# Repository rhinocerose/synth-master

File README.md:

# Synth Resouorce (Mostly Eurorack)

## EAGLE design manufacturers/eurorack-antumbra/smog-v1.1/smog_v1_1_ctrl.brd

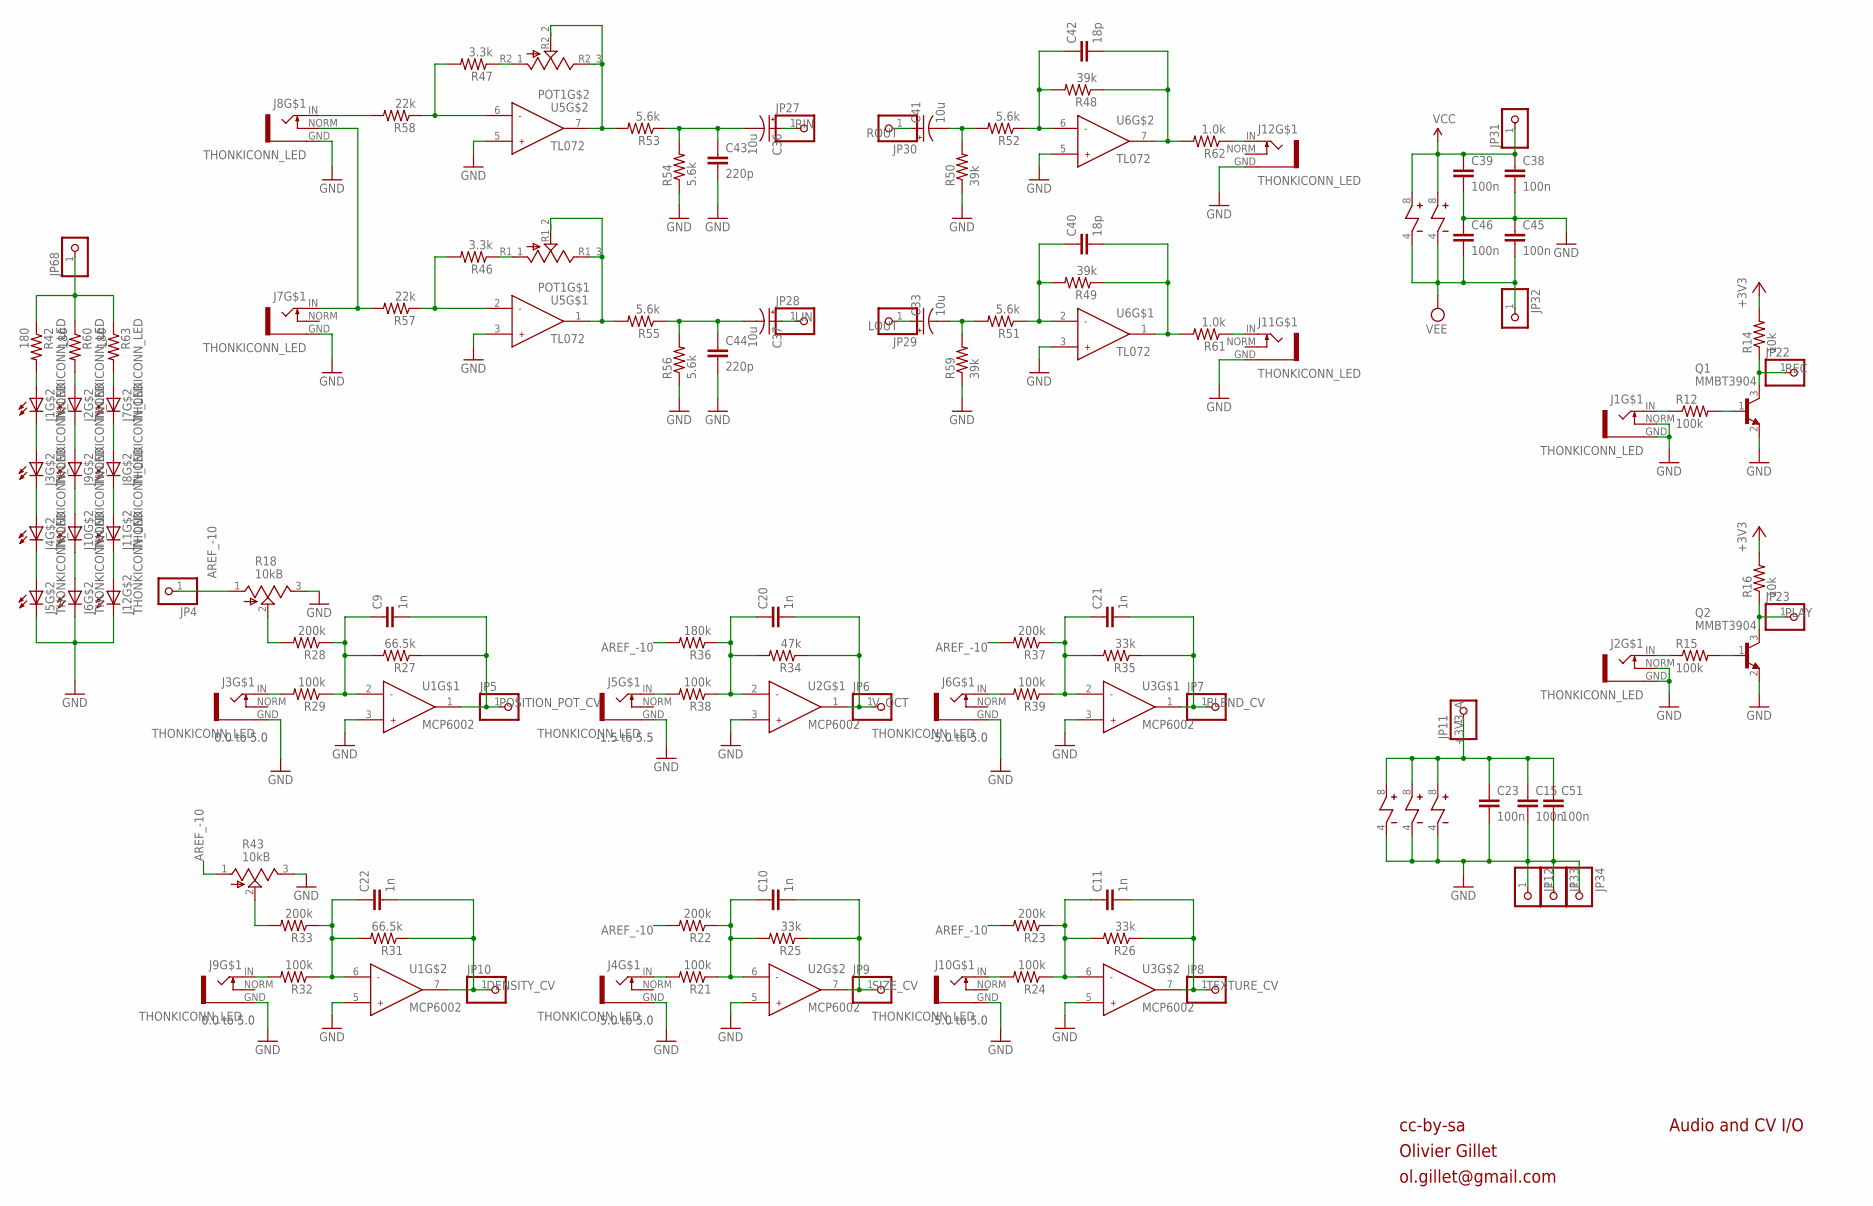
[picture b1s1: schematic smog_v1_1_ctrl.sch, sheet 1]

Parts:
C9, C10, C11, C20, C21, C22: 1n; RESISTOR_0603
C15, C23, C38, C39, C45, C46, C51: 100n; RESISTOR_0603
C33, C36, C37, C41: 10u; PANASONIC_B
C40, C42: 18p; RESISTOR_0603
C43, C44: 220p; RESISTOR_0603
J1, J2, J3, J4, J5, J6, J7, J8, J9, J10, J11, J12: THONKICONN_LED; LED_JACK
JP4, JP5, JP6, JP7, JP8, JP9, JP10, JP11, JP12, JP22, JP23, JP27, JP28, JP29, JP30, JP31, JP32, JP33, JP34, JP68: PINHD-1X1; 1X01
POT1: POT_DUAL_THONK
Q1, Q2: MMBT3904; SOT23
R12, R15, R21, R24, R29, R32, R38, R39: 100k; RESISTOR_0603
R14, R16: 10k; RESISTOR_0603
R18, R43: 10kB; ALPS_POT_VERTICAL
R22, R23, R28, R33, R37: 200k; RESISTOR_0603
R25, R26, R35: 33k; RESISTOR_0603
R27, R31: 66.5k; RESISTOR_0603
R34: 47k; RESISTOR_0603
R36: 180k; RESISTOR_0603
R42, R60, R63: 180; RESISTOR_0603
R46, R47: 3.3k; RESISTOR_0603
R48, R49, R50, R59: 39k; RESISTOR_0603
R51, R52, R53, R54, R55, R56: 5.6k; RESISTOR_0603
R57, R58: 22k; RESISTOR_0603
R61, R62: 1.0k; RESISTOR_0603
U1, U2, U3: MCP6002; SOIC8
U5, U6: TL072; SOIC8

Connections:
+3V3: R14.2, R16.2; also elsewhere on the board
+3V3_A: C15.1, C23.1, C51.1, JP11.1, U1.8, U2.8, U3.8; also elsewhere on the board
AREF_-10: JP4.1, R18.1 (A), R22.2, R23.2, R36.2, R37.2, R43.1 (A)
BLEND_CV: C21.2, JP7.1, R35.1, U3.1
DENSITY_CV: C22.2, JP10.1, R31.1, U1.7
GND: C15.2, C23.2, C38.2, C39.2, C43.2, C44.2, C45.1, C46.1, C51.2, J1.GND, J1.NORM, J2.GND, J2.NORM, J3.GND, J4.GND, J5.C, J5.GND, J6.C, J6.GND, J7.GND, J8.GND, J9.GND, J10.GND, J11.GND, J12.C, J12.GND, JP12.1, JP33.1, JP34.1, Q1.2 (E), Q2.2 (E), R18.3 (B), R43.3 (B), R50.1, R54.1, R56.1, R59.1, U1.3, U1.4, U1.5, U2.3, U2.4, U2.5, U3.3, U3.4, U3.5, U5.3, U5.5, U6.3, U6.5; also elsewhere on the board
LIN: C37.+, JP28.1
LOUT: C33.+, JP29.1
LOUT_JACK: J11.IN, R61.1
unnamed: J4.IN, R21.2
unnamed: C10.1, R21.1, R22.1, R25.2, U2.6
unnamed: J1.C, J3.A
unnamed: J10.IN, R24.2
unnamed: C11.1, R23.1, R24.1, R26.2, U3.6
unnamed: J6.IN, R39.2
unnamed: J3.C, J4.A
unnamed: J4.C, J5.A
unnamed: J5.IN, R38.2
unnamed: C20.1, R34.2, R36.1, R38.1, U2.2
unnamed: J2.A, R60.2
unnamed: J9.IN, R32.2
unnamed: C21.1, R35.2, R37.1, R39.1, U3.2
unnamed: J2.C, J9.A
unnamed: C37.-, C44.1, R55.1, R56.2
unnamed: J9.C, J10.A
unnamed: J8.IN, R58.2
unnamed: J7.IN, J8.NORM, R57.2
unnamed: C36.-, C43.1, R53.1, R54.2
unnamed: C41.-, R50.2, R52.2
unnamed: C22.1, R31.2, R32.1, R33.1, U1.6
unnamed: C42.1, R48.2, R52.1, U6.6
unnamed: R33.2, R43.2 (W)
unnamed: J3.IN, R29.2
unnamed: C42.2, R48.1, R62.2, U6.7
unnamed: C9.1, R27.2, R28.1, R29.1, U1.2
unnamed: C33.-, R51.2, R59.2
unnamed: C40.1, R49.2, R51.1, U6.2
unnamed: C40.2, R49.1, R61.2, U6.1
unnamed: R18.2 (W), R28.2
unnamed: J2.IN, R15.1
unnamed: Q2.1 (B), R15.2
unnamed: POT1.R2_2 (W), POT1.R2_3 (B), R53.2, U5.7
unnamed: POT1.R1_2 (W), POT1.R1_3 (B), R55.2, U5.1
unnamed: POT1.R2_1 (A), R47.1
unnamed: POT1.R1_1 (A), R46.1
unnamed: R47.2, R58.1, U5.6
unnamed: J6.A, J10.C
unnamed: J7.A, R63.2
unnamed: J1.IN, R12.1
unnamed: R46.2, R57.1, U5.2
unnamed: J7.C, J8.A
unnamed: J8.C, J11.A
unnamed: J11.C, J12.A
unnamed: J1.A, R42.2
unnamed: Q1.1 (B), R12.2
unnamed: JP68.1, R42.1, R60.1, R63.1
PLAY: JP23.1, Q2.3 (C), R16.1
POSITION_POT_CV: C9.2, JP5.1, R27.1, U1.1
REC: JP22.1, Q1.3 (C), R14.1
RIN: C36.+, JP27.1
ROUT: C41.+, JP30.1
ROUT_JACK: J12.IN, R62.1
SIZE_CV: C10.2, JP9.1, R25.1, U2.7
TEXTURE_CV: C11.2, JP8.1, R26.1, U3.7
VCC: C38.1, C39.1, JP31.1, U5.8, U6.8
VEE: C45.2, C46.2, JP32.1, U5.4, U6.4
V_OCT: C20.2, JP6.1, R34.1, U2.1

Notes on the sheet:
cc-by-sa
Olivier Gillet
ol.gillet@gmail.com
Audio and CV I/O
0.0 to 5.0
-1.5 to 5.5
-5.0 to 5.0

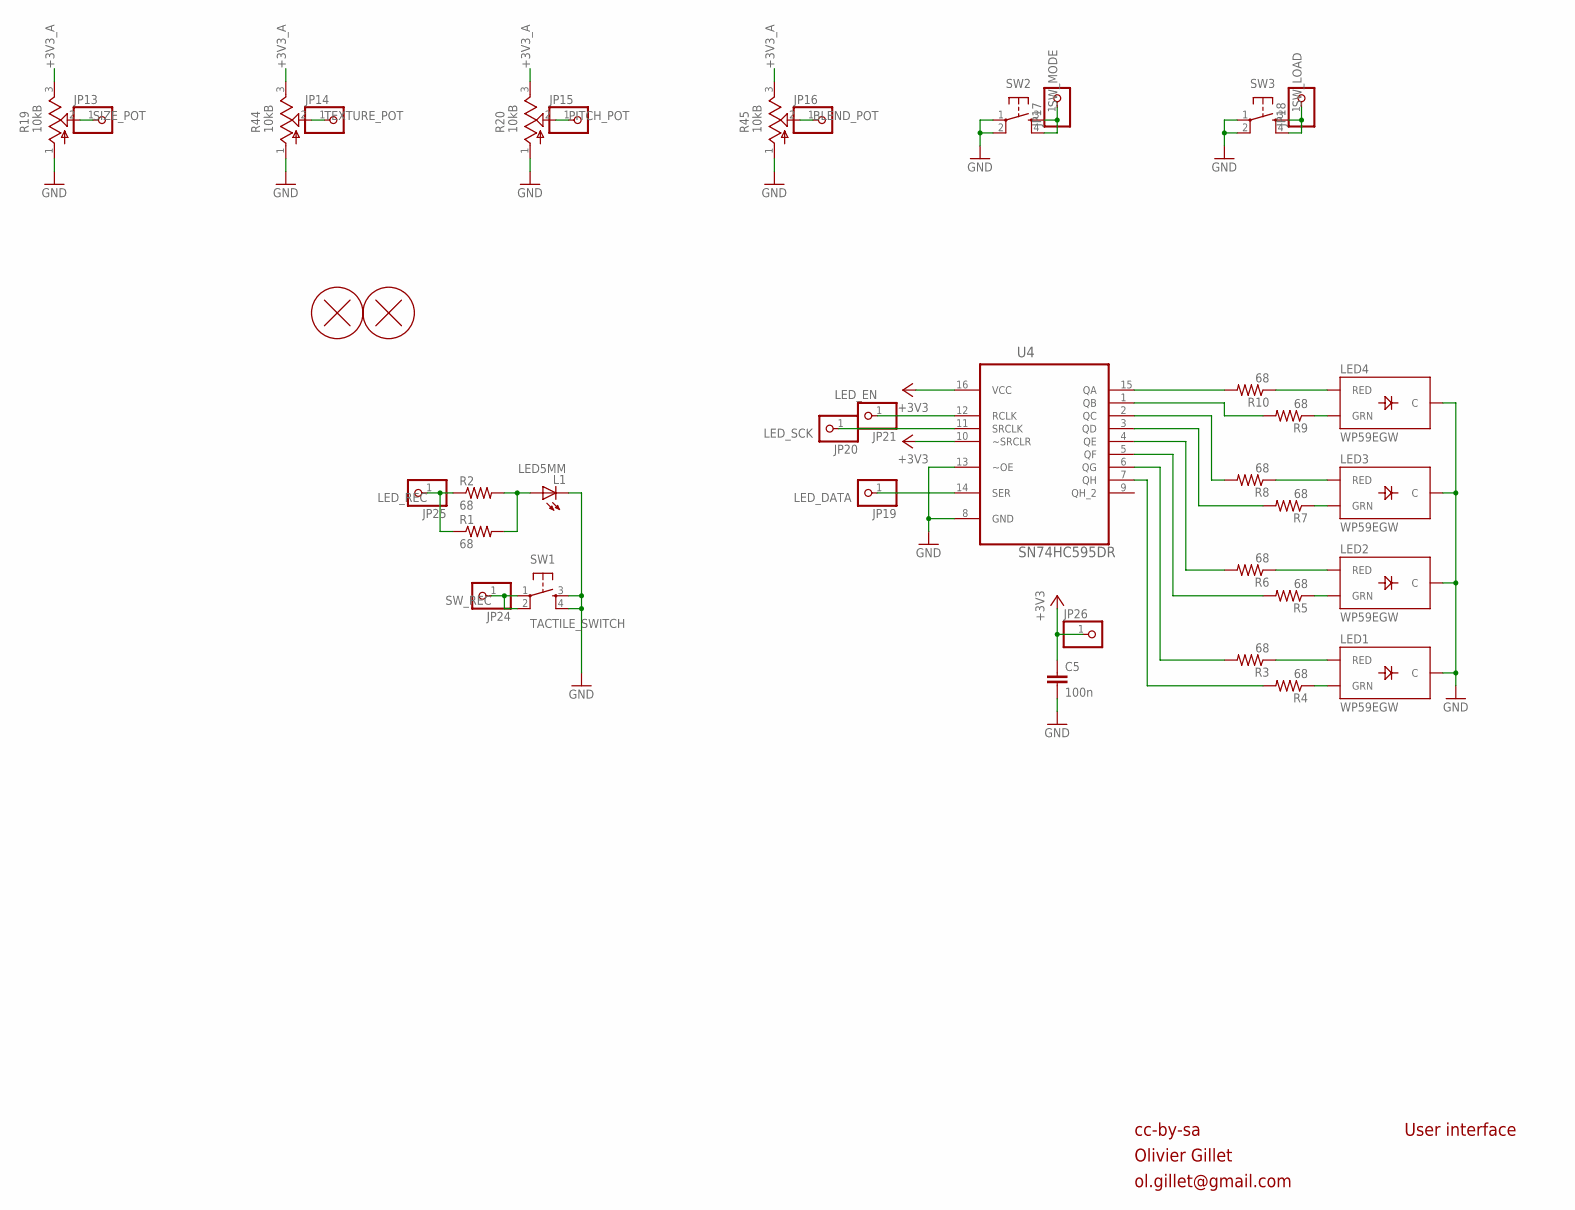
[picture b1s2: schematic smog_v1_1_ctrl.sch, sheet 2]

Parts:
C5: 100n; RESISTOR_0603
H1, H2: PCB_SCREW
JP13, JP14, JP15, JP16, JP17, JP18, JP19, JP20, JP21, JP24, JP25, JP26: PINHD-1X1; 1X01
L1: LED5MM; LED_5MM
LED1, LED2, LED3, LED4: WP59EGW; LED_BICOLOR
R1, R2, R3, R4, R5, R6, R7, R8, R9, R10: 68; RESISTOR_0603
R19, R20, R44, R45: 10kB; ALPS_POT_VERTICAL
SW1, SW2, SW3: TACTILE_SWITCH; TACTILE-PTH
U4: SN74HC595DR; SOIC16

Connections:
+3V3: C5.1, JP26.1, U4.10 (~SRCLR), U4.16 (VCC); also elsewhere on the board
+3V3_A: R19.3 (B), R20.3 (B), R44.3 (B), R45.3 (B); also elsewhere on the board
BLEND_POT: JP16.1, R45.2 (W)
GND: C5.2, L1.K (C), LED1.2 (C), LED2.2 (C), LED3.2 (C), LED4.2 (C), R19.1 (A), R20.1 (A), R44.1 (A), R45.1 (A), SW1.3, SW1.4, SW2.1, SW2.2, SW3.1, SW3.2, U4.8 (GND), U4.13 (~OE); also elsewhere on the board
LED_DATA: JP19.1, U4.14 (SER)
LED_EN: JP21.1, U4.12 (RCLK)
LED_REC: JP25.1, R1.1, R2.1
LED_SCK: JP20.1, U4.11 (SRCLK)
unnamed: LED4.1 (GRN), R9.1
unnamed: LED4.3 (RED), R10.1
unnamed: LED3.3 (RED), R8.1
unnamed: LED3.1 (GRN), R7.1
unnamed: LED2.3 (RED), R6.1
unnamed: L1.A, R1.2, R2.2
unnamed: LED2.1 (GRN), R5.1
unnamed: LED1.3 (RED), R3.1
unnamed: LED1.1 (GRN), R4.1
unnamed: R10.2, U4.15 (QA)
unnamed: R9.2, U4.1 (QB)
unnamed: R8.2, U4.2 (QC)
unnamed: R7.2, U4.3 (QD)
unnamed: R6.2, U4.4 (QE)
unnamed: R5.2, U4.5 (QF)
unnamed: R3.2, U4.6 (QG)
unnamed: R4.2, U4.7 (QH)
PITCH_POT: JP15.1, R20.2 (W)
SIZE_POT: JP13.1, R19.2 (W)
SW_LOAD: JP18.1, SW3.3, SW3.4
SW_MODE: JP17.1, SW2.3, SW2.4
SW_REC: JP24.1, SW1.1, SW1.2
TEXTURE_POT: JP14.1, R44.2 (W)

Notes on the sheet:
cc-by-sa
Olivier Gillet
ol.gillet@gmail.com
User interface

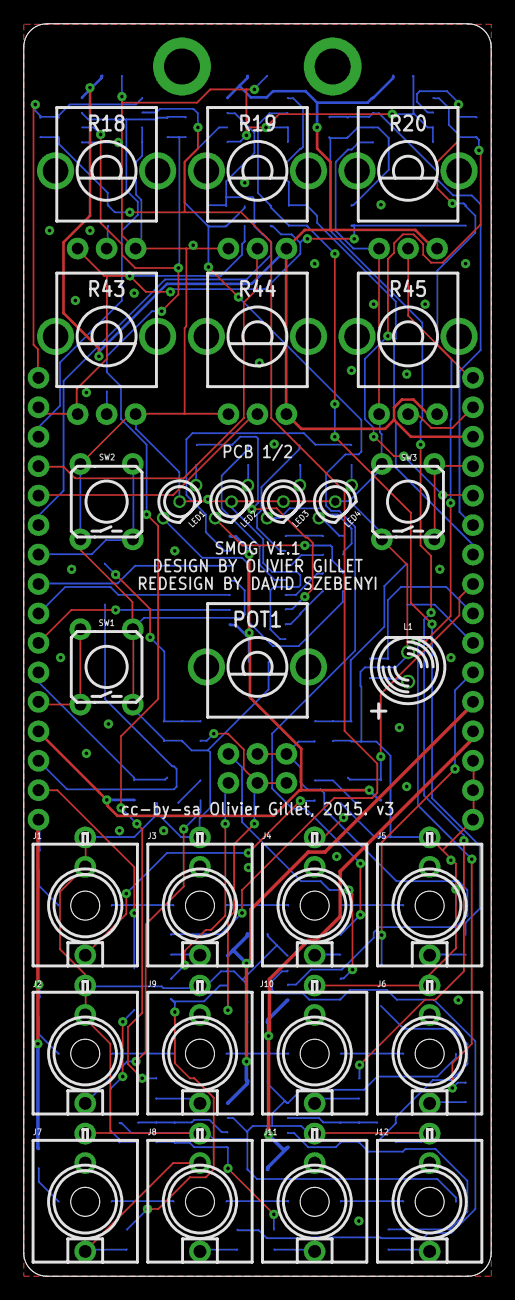
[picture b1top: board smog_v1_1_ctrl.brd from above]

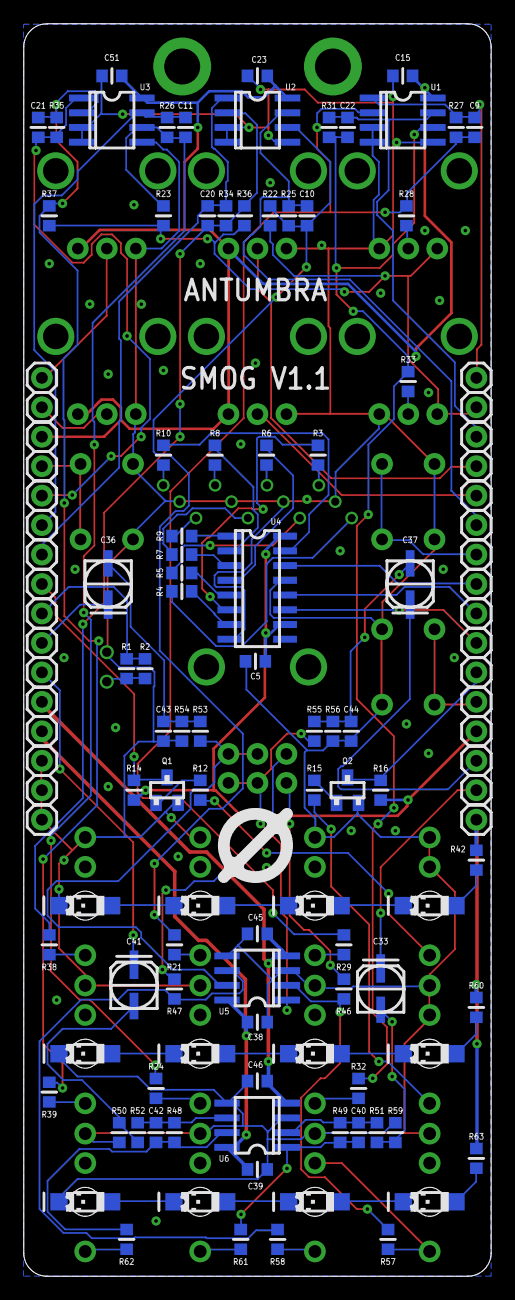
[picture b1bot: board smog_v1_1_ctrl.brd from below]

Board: 2 copper layers, 40.3 x 108.0 mm, 143 parts (114 on the bottom side), 95 nets.

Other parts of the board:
U$1: LOGO_6.5

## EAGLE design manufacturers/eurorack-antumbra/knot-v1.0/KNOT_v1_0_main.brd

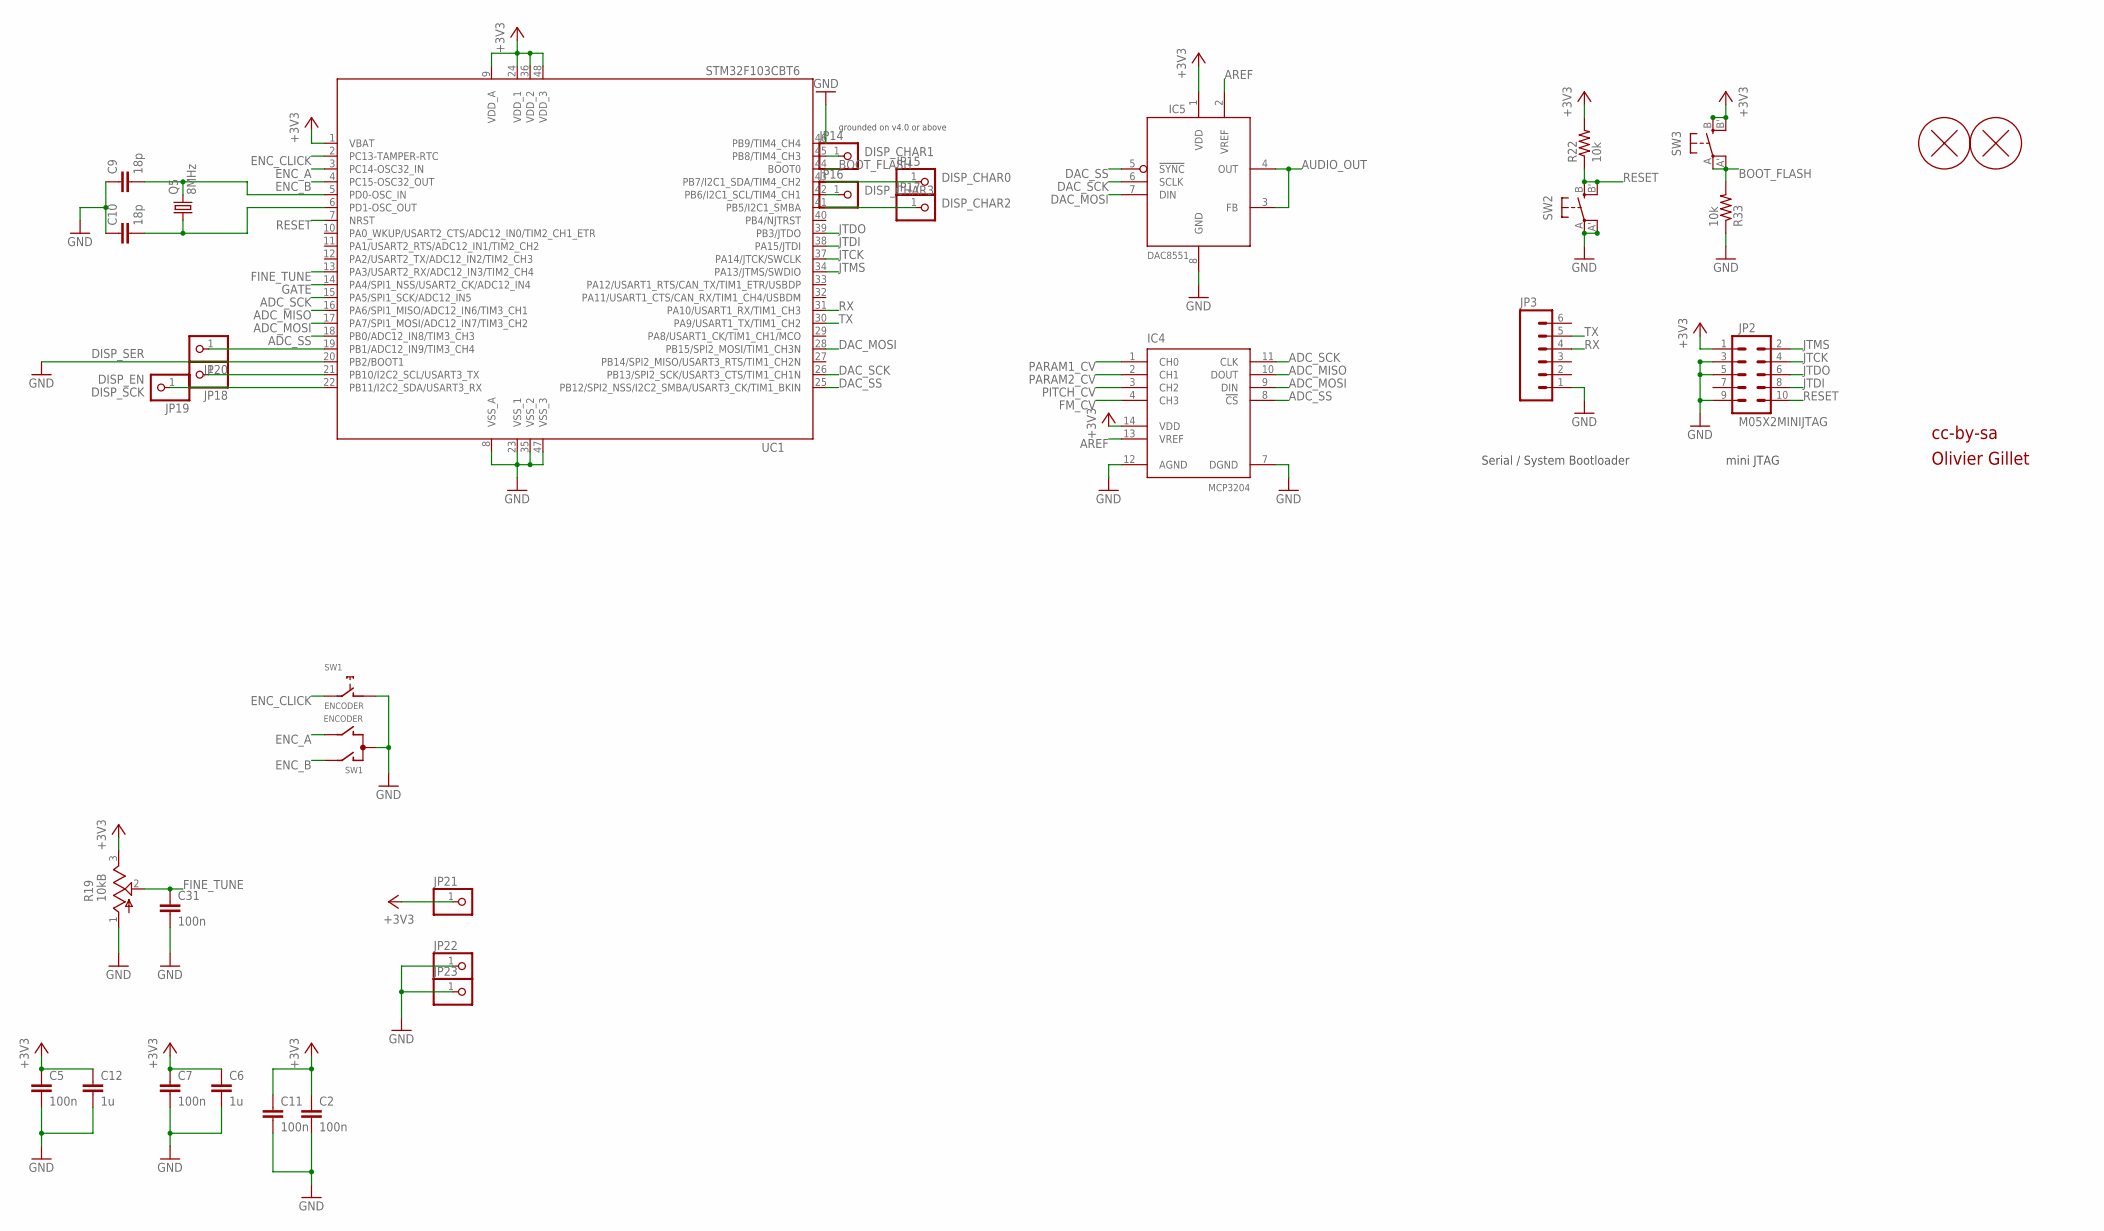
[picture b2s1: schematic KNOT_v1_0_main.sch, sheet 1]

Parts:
C2, C5, C7, C11, C31: 100n; RESISTOR_0603
C6, C12: 1u; RESISTOR_0603
C9, C10: 18p; RESISTOR_0603
H1, H2: PCB_SCREW
IC4: MCP3204; SO14
IC5: DAC8551; MSOP-8
JP2: M05X2MINIJTAG; 2X5-1.27
JP3: M06SIP; 1X06
JP14, JP15, JP16, JP17, JP18, JP19, JP20, JP21, JP22, JP23: PINHD-1X1; 1X01
Q5: 8MHz; HC49UP
R19: 10kB; ALPS_POT_VERTICAL
R22, R33: 10k; RESISTOR_0603
SW1: ENCODER; ALPS_EC12E_SW
SW2, SW3: EVQQ2; EVQ-Q2
UC1: STM32F103CBT6; LQFP48

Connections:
+3V3: C2.1, C5.1, C6.1, C7.1, C11.1, C12.1, IC4.14 (VDD), IC5.1 (VDD), JP2.1, JP21.1, R19.3 (B), R22.2, SW3.B (S), SW3.B' (S1), UC1.1 (VBAT), UC1.9 (VDD_A), UC1.24 (VDD_1), UC1.36 (VDD_2), UC1.48 (VDD_3); also elsewhere on the board
ADC_MISO: IC4.10 (DOUT), UC1.16 (PA6/SPI1_MISO/ADC12_IN6/TIM3_CH1)
ADC_MOSI: IC4.9 (DIN), UC1.17 (PA7/SPI1_MOSI/ADC12_IN7/TIM3_CH2)
ADC_SCK: IC4.11 (CLK), UC1.15 (PA5/SPI1_SCK/ADC12_IN5)
ADC_SS: IC4.8 (!CS), UC1.18 (PB0/ADC12_IN8/TIM3_CH3)
AREF: IC4.13 (VREF), IC5.2 (VREF); also elsewhere on the board
AUDIO_OUT: IC5.3 (FB), IC5.4 (OUT); also elsewhere on the board
BOOT_FLASH: R33.2, SW3.A, SW3.A' (P1), UC1.44 (BOOT0)
DAC_MOSI: IC5.7 (DIN), UC1.28 (PB15/SPI2_MOSI/TIM1_CH3N)
DAC_SCK: IC5.6 (SCLK), UC1.26 (PB13/SPI2_SCK/USART3_CTS/TIM1_CH1N)
DAC_SS: IC5.5 (!SYNC), UC1.25 (PB12/SPI2_NSS/I2C2_SMBA/USART3_CK/TIM1_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)
DISP_CHAR0: JP15.1, UC1.43 (PB7/I2C1_SDA/TIM4_CH2)
DISP_CHAR1: JP14.1, UC1.45 (PB8/TIM4_CH3)
DISP_CHAR2: JP17.1, UC1.41 (PB5/I2C1_SMBA)
DISP_CHAR3: JP16.1, UC1.42 (PB6/I2C1_SCL/TIM4_CH1)
DISP_EN: JP18.1, UC1.21 (PB10/I2C2_SCL/USART3_TX)
DISP_SCK: JP19.1, UC1.22 (PB11/I2C2_SDA/USART3_RX)
DISP_SER: JP20.1, UC1.19 (PB1/ADC12_IN9/TIM3_CH4)
ENC_A: SW1.B, UC1.3 (PC14-OSC32_IN)
ENC_B: SW1.A, UC1.4 (PC15-OSC32_OUT)
ENC_CLICK: SW1.E (2), UC1.2 (PC13-TAMPER-RTC)
FINE_TUNE: C31.1, R19.2 (W), UC1.13 (PA3/USART2_RX/ADC12_IN3/TIM2_CH4)
FM_CV: IC4.4 (CH3); also elsewhere on the board
GATE: UC1.14 (PA4/SPI1_NSS/USART2_CK/ADC12_IN4); also elsewhere on the board
GND: C2.2, C5.2, C6.2, C7.2, C9.1, C10.1, C11.2, C12.2, C31.2, IC4.7 (DGND), IC4.12 (AGND), IC5.8 (GND), JP2.3, JP2.5, JP2.9, JP3.1, JP22.1, JP23.1, R19.1 (A), R33.1, SW1.C, SW1.D (1), SW2.A, SW2.A' (P1), UC1.8 (VSS_A), UC1.20 (PB2/BOOT1), UC1.23 (VSS_1), UC1.35 (VSS_2), UC1.46 (PB9/TIM4_CH4), UC1.47 (VSS_3); also elsewhere on the board
JTCK: JP2.4, UC1.37 (PA14/JTCK/SWCLK)
JTDI: JP2.8, UC1.38 (PA15/JTDI)
JTDO: JP2.6, UC1.39 (PB3/JTDO)
JTMS: JP2.2, UC1.34 (PA13/JTMS/SWDIO)
unnamed: C9.2, Q5.2, UC1.5 (PD0-OSC_IN)
unnamed: C10.2, Q5.1, UC1.6 (PD1-OSC_OUT)
PARAM1_CV: IC4.1 (CH0); also elsewhere on the board
PARAM2_CV: IC4.2 (CH1); also elsewhere on the board
PITCH_CV: IC4.3 (CH2); also elsewhere on the board
RESET: JP2.10, R22.1, SW2.B (S), SW2.B' (S1), UC1.7 (NRST)
RX: JP3.4, UC1.31 (PA10/USART1_RX/TIM1_CH3)
TX: JP3.5, UC1.30 (PA9/USART1_TX/TIM1_CH2)

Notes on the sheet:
Serial / System Bootloader
mini JTAG
grounded on v4.0 or above
cc-by-sa
Olivier Gillet

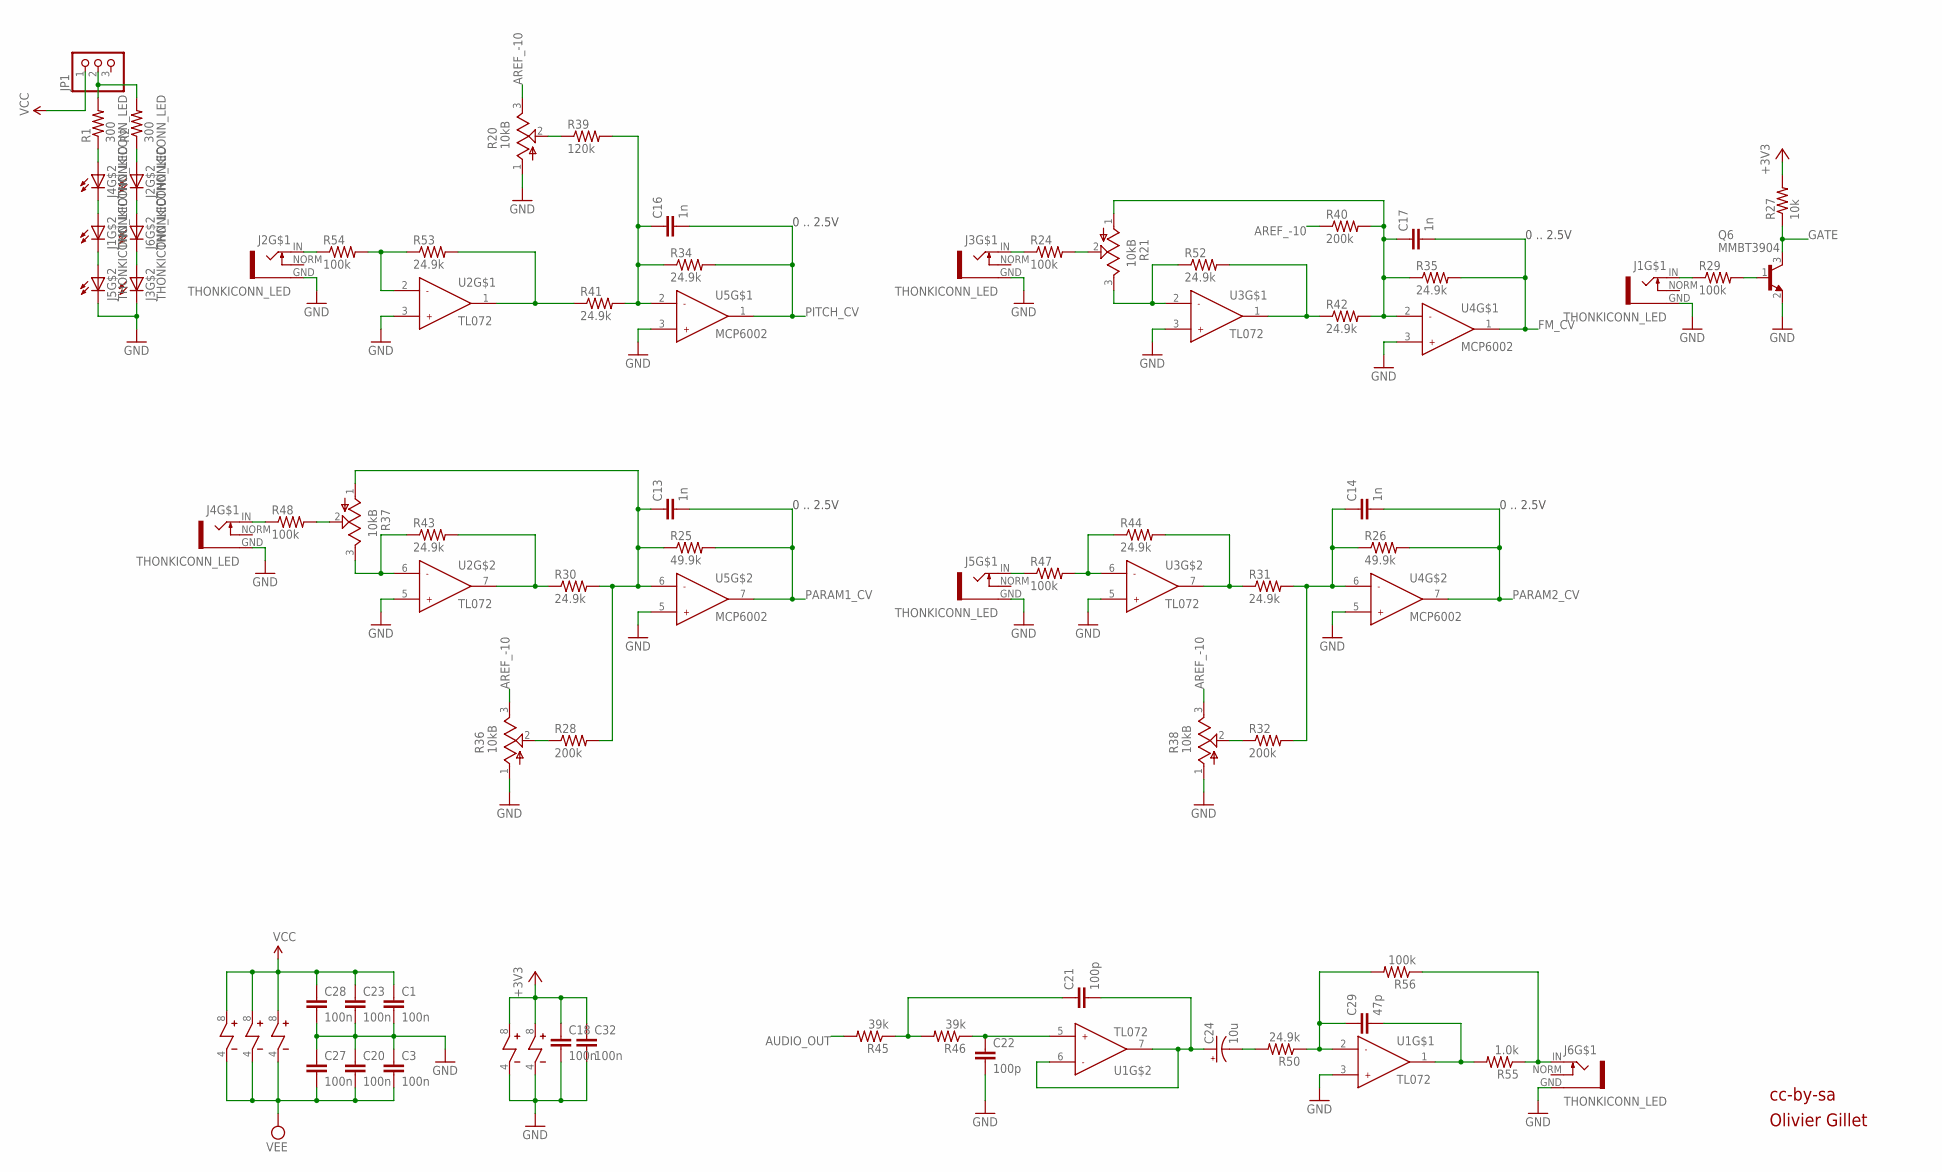
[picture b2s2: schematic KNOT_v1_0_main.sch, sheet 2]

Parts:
C1, C3, C18, C20, C23, C27, C28, C32: 100n; RESISTOR_0603
C13, C14, C16, C17: 1n; RESISTOR_0603
C21, C22: 100p; RESISTOR_0603
C24: 10u; PANASONIC_B
C29: 47p; RESISTOR_0603
J1, J2, J3, J4, J5, J6: THONKICONN_LED; LED_JACK
JP1: PINHD-1X3; 1X03
Q6: MMBT3904; SOT23
R1, R2: 300; RESISTOR_0603
R20, R21, R36, R37, R38: 10kB; ALPS_POT_VERTICAL
R24, R29, R47, R48, R54, R56: 100k; RESISTOR_0603
R25, R26: 49.9k; RESISTOR_0603
R27: 10k; RESISTOR_0603
R28, R32, R40: 200k; RESISTOR_0603
R30, R31, R34, R35, R41, R42, R43, R44, R50, R52, R53: 24.9k; RESISTOR_0603
R39: 120k; RESISTOR_0603
R45, R46: 39k; RESISTOR_0603
R55: 1.0k; RESISTOR_0603
U1, U2, U3: TL072; SOIC8
U4, U5: MCP6002; SOIC8

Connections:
+3V3: C18.1, C32.1, R27.2, U4.8, U5.8; also elsewhere on the board
AREF_-10: R20.3 (B), R36.3 (B), R38.3 (B), R40.1; also elsewhere on the board
AUDIO_OUT: R45.2; also elsewhere on the board
FM_CV: C17.2, R35.2, U4.1; also elsewhere on the board
GATE: Q6.3 (C), R27.1; also elsewhere on the board
GND: C1.2, C3.1, C18.2, C20.1, C22.2, C23.2, C27.1, C28.2, C32.2, J1.GND, J2.GND, J3.C, J3.GND, J4.GND, J5.C, J5.GND, J6.GND, Q6.2 (E), R20.1 (A), R36.1 (A), R38.1 (A), U1.3, U2.3, U2.5, U3.3, U3.5, U4.3, U4.4, U4.5, U5.3, U5.4, U5.5; also elsewhere on the board
unnamed: J3.A, J6.C
unnamed: J2.C, J6.A
unnamed: J2.A, R2.1
unnamed: J1.C, J5.A
unnamed: J1.A, J4.C
unnamed: J4.A, R1.1
unnamed: JP1.2, R1.2, R2.2
unnamed: R41.1, R53.2, U2.1
unnamed: R20.2 (W), R39.1
unnamed: J2.IN, R54.1
unnamed: C16.1, R34.1, R39.2, R41.2, U5.2
unnamed: R53.1, R54.2, U2.2
unnamed: J3.IN, R24.1
unnamed: J4.IN, R48.1
unnamed: R21.2 (W), R24.2
unnamed: R37.3 (B), R43.1, U2.6
unnamed: R30.1, R43.2, U2.7
unnamed: R21.3 (B), R52.1, U3.2
unnamed: R42.1, R52.2, U3.1
unnamed: C17.1, R21.1 (A), R35.1, R40.2, R42.2, U4.2
unnamed: J1.IN, R29.1
unnamed: R31.1, R44.2, U3.7
unnamed: C13.1, R25.1, R28.2, R30.2, R37.1 (A), U5.6
unnamed: J5.IN, R47.1
unnamed: R28.1, R36.2 (W)
unnamed: R37.2 (W), R48.2
unnamed: R44.1, R47.2, U3.6
unnamed: R32.1, R38.2 (W)
unnamed: Q6.1 (B), R29.2
unnamed: C21.2, C24.+, U1.6, U1.7
unnamed: C24.-, R50.2
unnamed: C22.1, R46.1, U1.5
unnamed: C14.1, R26.1, R31.2, R32.2, U4.6
unnamed: C21.1, R45.1, R46.2
unnamed: J6.IN, R55.1, R56.1
unnamed: C29.2, R55.2, U1.1
unnamed: C29.1, R50.1, R56.2, U1.2
PARAM1_CV: C13.2, R25.2, U5.7; also elsewhere on the board
PARAM2_CV: C14.2, R26.2, U4.7; also elsewhere on the board
PITCH_CV: C16.2, R34.2, U5.1; also elsewhere on the board
VCC: C1.1, C23.1, C28.1, JP1.1, U1.8, U2.8, U3.8; also elsewhere on the board
VEE: C3.2, C20.2, C27.2, U1.4, U2.4, U3.4; also elsewhere on the board

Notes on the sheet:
0 .. 2.5V
cc-by-sa
Olivier Gillet

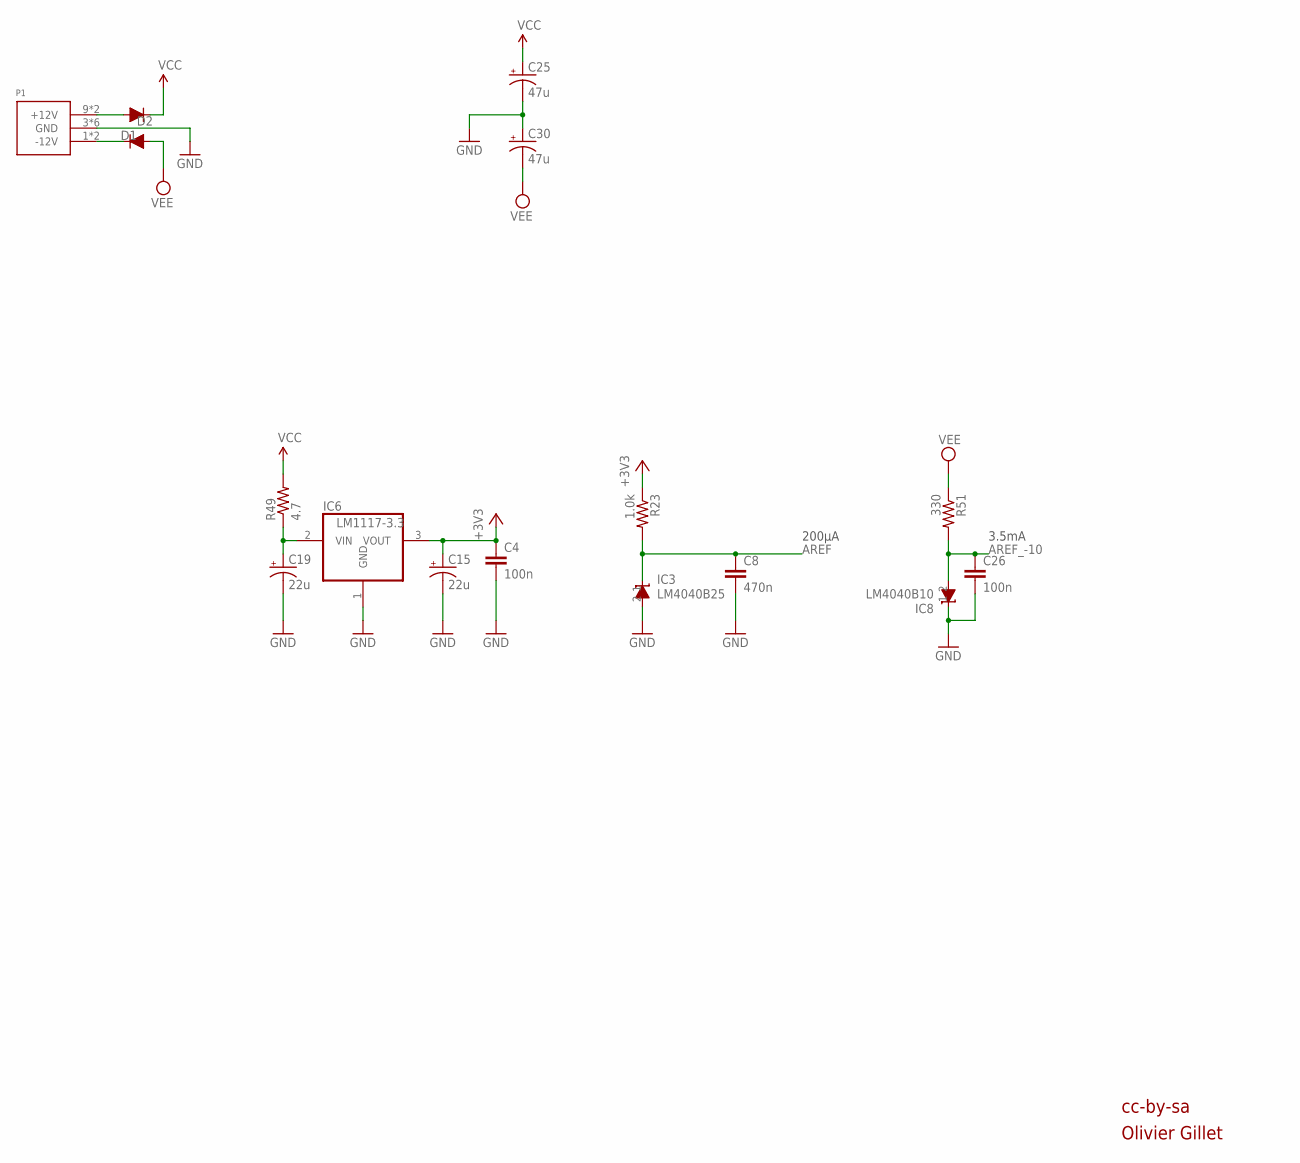
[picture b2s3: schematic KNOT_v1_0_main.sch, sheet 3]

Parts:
C4, C26: 100n; RESISTOR_0603
C8: 470n; RESISTOR_0603
C15, C19: 22u; PANASONIC_D
C25, C30: 47u; PANASONIC_D
D1, D2: 1N5819HW; SOD123
IC3: LM4040B25; SOT23
IC6: LM1117-3.3; TO252
IC8: LM4040B10; SOT23
P1: POWER_SIMPLE10; POWER_10
R23: 1.0k; RESISTOR_0603
R49: 4.7; RESISTOR_0603
R51: 330; RESISTOR_0603

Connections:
+3V3: C4.1, C15.+, IC6.3 (VOUT), R23.1; also elsewhere on the board
AREF: C8.1, IC3.1 (C), R23.2; also elsewhere on the board
AREF_-10: C26.1, IC8.2 (A), R51.2; also elsewhere on the board
GND: C4.2, C8.2, C15.-, C19.-, C25.-, C26.2, C30.+, IC3.2 (A), IC6.1 (GND), IC8.1 (C), P1.3 (GND), P1.4 (GND), P1.5 (GND), P1.6 (GND), P1.7 (GND), P1.8 (GND); also elsewhere on the board
unnamed: D1.+, P1.9 (+12V), P1.10 (+12V)
unnamed: D2.-, P1.1 (-12V), P1.2 (-12V)
unnamed: C19.+, IC6.2 (VIN), R49.1
VCC: C25.+, D1.-, R49.2; also elsewhere on the board
VEE: C30.-, D2.+, R51.1; also elsewhere on the board

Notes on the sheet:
3.5mA
200µA
cc-by-sa
Olivier Gillet

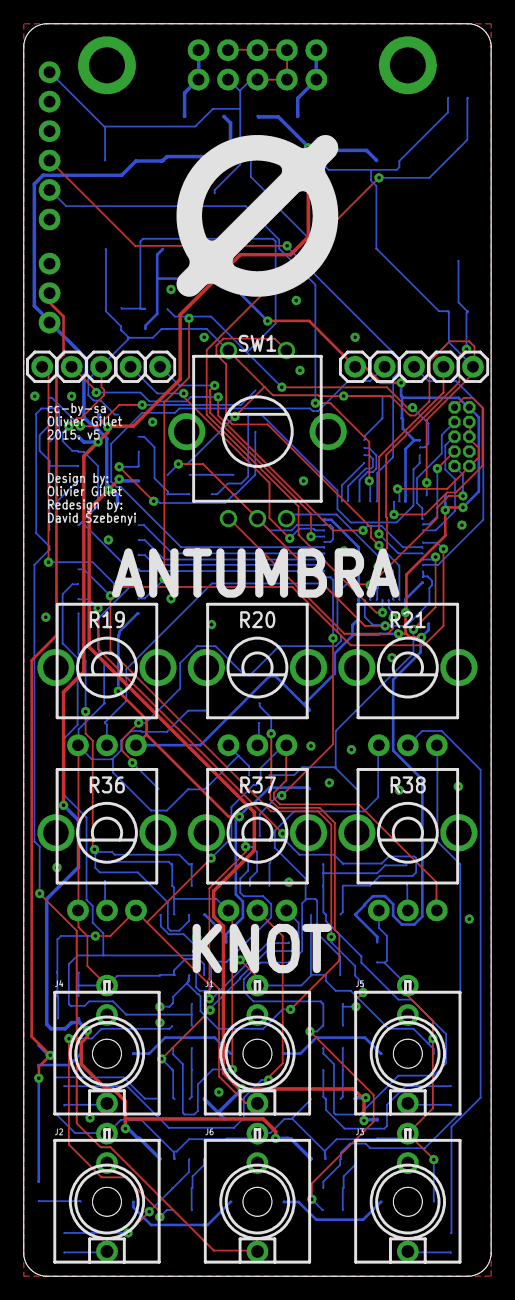
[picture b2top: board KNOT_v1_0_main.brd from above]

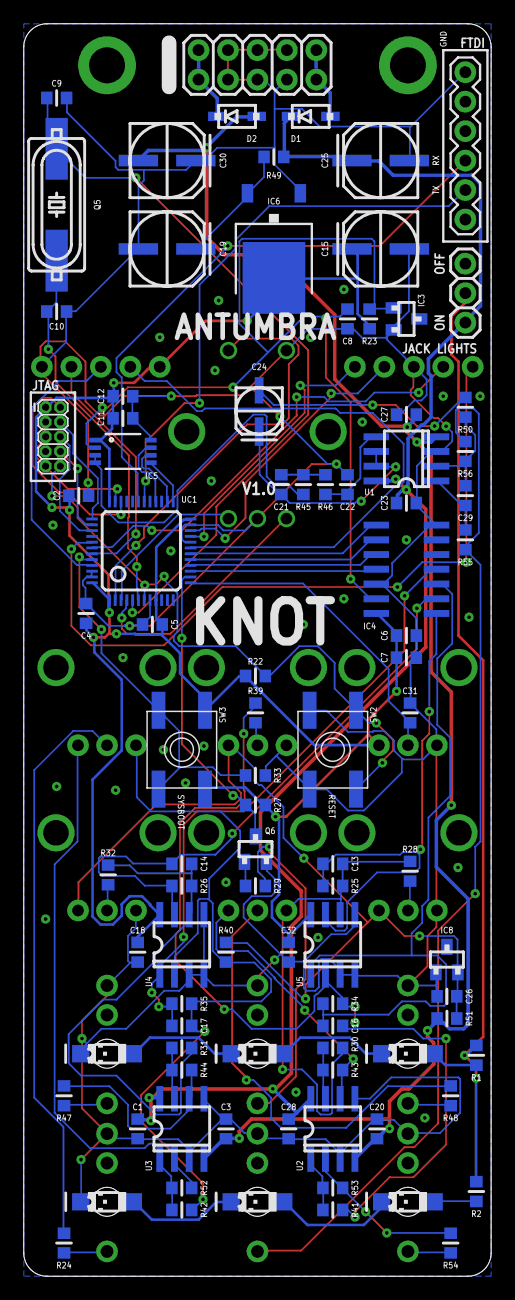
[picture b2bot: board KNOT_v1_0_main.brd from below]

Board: 2 copper layers, 40.3 x 108.0 mm, 113 parts (87 on the bottom side), 80 nets.

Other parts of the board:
U$1: LOGO_14

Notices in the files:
manufacturers/eurorack-antumbra/smog-v1.1/smog_v1_1_brain.brd:
cc-by-sa Olivier Gillet, 2015. v3
